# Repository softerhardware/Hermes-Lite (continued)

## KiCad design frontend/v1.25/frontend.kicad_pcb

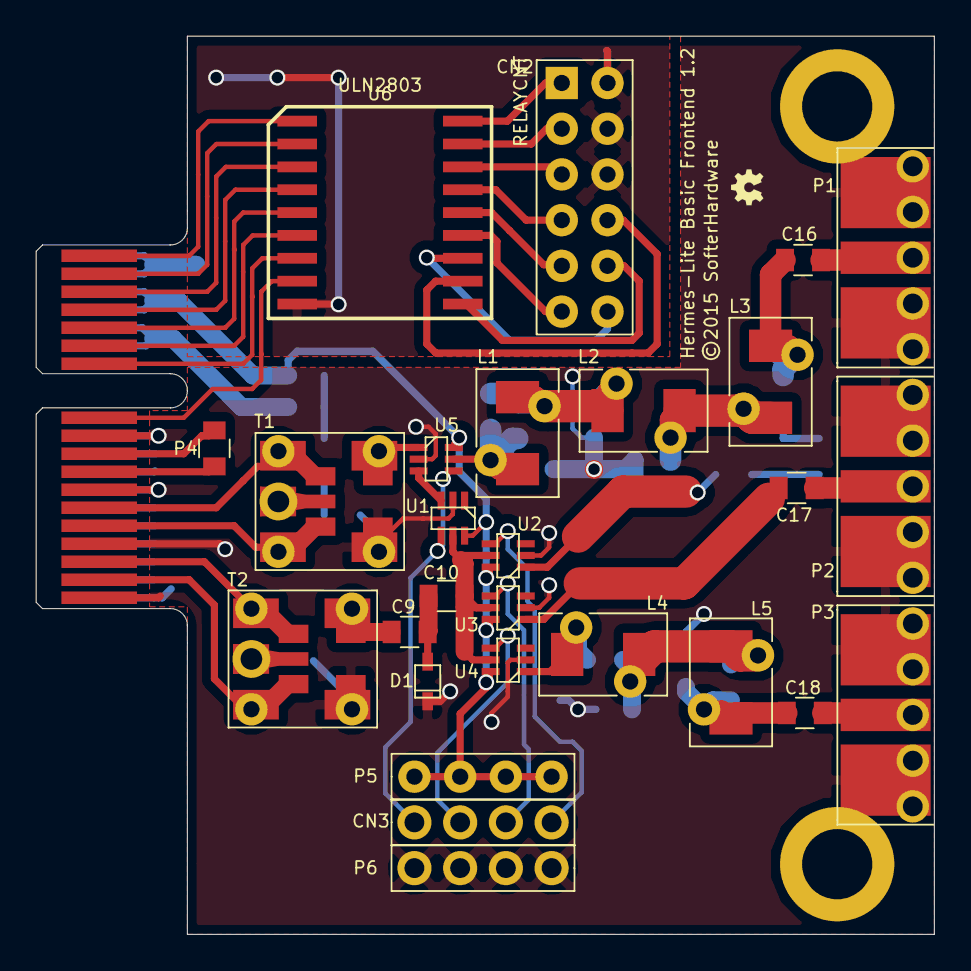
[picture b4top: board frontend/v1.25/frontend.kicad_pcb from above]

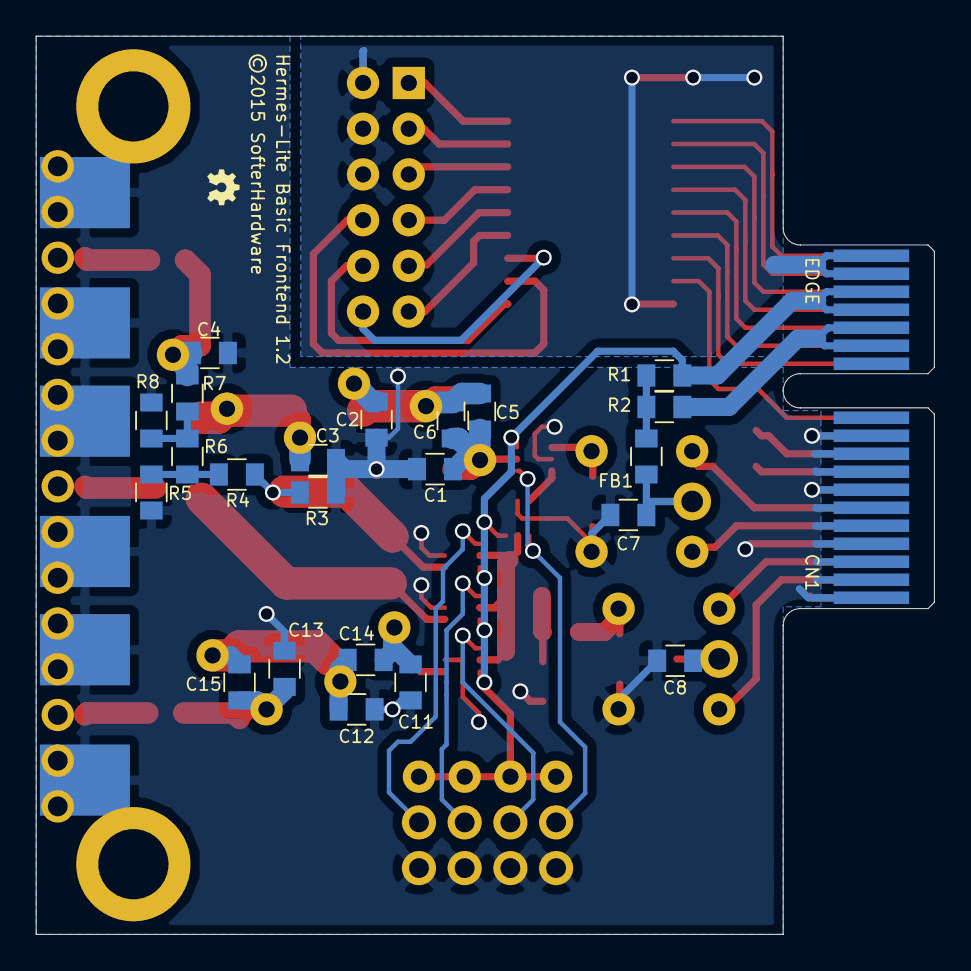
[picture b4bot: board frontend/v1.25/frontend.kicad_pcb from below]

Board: 2 copper layers, 49.9 x 49.9 mm, 52 parts (23 on the bottom side), 53 nets.

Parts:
C1: 110pF; C_0805
C2: 220pF; C_0805
C3: 160pF; C_0805
C4, C14, C15: DNI; C_0805
C5: 8.4pF; C_0805
C6: 75pF; C_0805
C7, C8, C9, C10, C16, C17, C18: 0.1uF; C_0805
C11, C13: 100pF; C_0805
C12: 180pF; C_0805
CN1: EDGE
CN2: RELAYCNT; BREAKOUT
CN3: RXCNT; 4pinmid
D1: DIODESCH2; SOD323
FB1: FB; C_0805
L1: 150nH; inductor
L2: 270nH; inductor
L3: 0H; inductor
L4, L5: 390nH; inductor
MH: VAL**; MH
MH#2: VAL**; MH
P1, P2, P3: SMA/BNC/HDR; rfconnector
P4: CONN_01X02; C_0805
P5, P6: CONN_01X04; 4pinmid
R1, R4: 0; C_0805
R2, R3: DNI; C_0805
R5: 87; C_0805
R6: 43; C_0805
R7: 2.2K; C_0805
R8: 76; C_0805
T1: 1:1; TRANSFSMT
T2: 8:1 Z; TRANSFSMT
U1, U2, U3, U4, U5: PE4259; pe4259
U6: ULN2803; PSOP-18

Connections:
3V: CN1.A15, CN1.A16, P5.1, P5.2, P5.3, P5.4, R1.1, U1.6, U2.6, U3.6, U4.6, U5.6
5V: CN1.A13, CN1.A14, R2.1
GND: C1.2, C2.2, C3.2, C4.2, C7.2, C8.2, C11.2, C12.2, C13.2, CN1.A1, CN1.A2, CN1.A3, CN1.A4, CN1.A5, CN1.A6, CN1.A7, CN1.A8, CN1.A9, CN1.A10, CN1.B1, CN1.B4, CN1.B7, CN1.B10, D1.2, P1.2, P2.2, P3.2, P6.1, P6.2, P6.3, P6.4, R3.2, R5.2, R8.2, T1.4, T2.4, U1.2, U2.2, U3.2, U4.2, U5.2
GNDREF: CN1.A17, CN1.A18, CN2.2, CN2.4, CN2.6, U6.9
unnamed: C1.1, C5.2, C6.2, L1.1, U5.5
unnamed: C2.1, C5.1, C6.1, L1.2, L2.1
unnamed: C3.1, L2.2, L3.1
unnamed: C7.1, FB1.1, T1.2
unnamed: C8.1, T2.2
unnamed: C9.2, T2.5
unnamed: C10.1, U1.5, U2.5, U3.5, U4.5
unnamed: C9.1, C10.2, D1.1
unnamed: C11.1, C14.2, L4.1, U4.1
unnamed: C12.1, C14.1, C15.2, L4.2, L5.1
unnamed: C13.1, C15.1, C18.1, L5.2
unnamed: C4.1, C16.1, L3.2, R7.2
unnamed: C16.2, P1.1
unnamed: C17.1, U3.1
unnamed: C17.2, P2.1
unnamed: C18.2, P3.1
unnamed: CN1.B2, T2.3
unnamed: CN1.B3, T2.1
unnamed: CN1.B5, T1.3
unnamed: CN1.B6, T1.1
unnamed: CN1.B8, P4.2
unnamed: CN1.B9, P4.1
unnamed: CN1.B11, U6.8
unnamed: CN1.B12, U6.7
unnamed: CN1.B13, U6.6
unnamed: CN1.B14, U6.5
unnamed: CN1.B15, U6.4
unnamed: CN1.B16, U6.3
unnamed: CN1.B17, U6.2
unnamed: CN1.B18, U6.1
unnamed: CN2.1, U6.18
unnamed: CN2.3, U6.17
unnamed: CN2.5, U6.16
unnamed: CN2.7, U6.15
unnamed: CN2.8, U6.11
unnamed: CN2.9, U6.14
unnamed: CN2.10, U6.10
unnamed: CN2.11, U6.13
unnamed: CN2.12, U6.12
unnamed: FB1.2, R1.2, R2.2
unnamed: R3.1, R4.2, U2.1
unnamed: R4.1, R5.1, R6.2
unnamed: R6.1, R7.1, R8.1
unnamed: T1.5, U5.1
unnamed: U1.3, U5.3
RX2: CN3.3, U3.4
RX3: CN3.2, U4.4
TAP: CN3.4, U2.4
TR: CN3.1, U1.4, U5.4

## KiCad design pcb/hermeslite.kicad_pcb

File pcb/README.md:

Hermes-Lite PCB
===============

This directory contains the following files document and build the Hermes-Lite hardware:

 * Kicad schematic
 * Kicad pcb 
 * High resolution photos of assembled prototoype (*.jpg)
 * BOM 
 * Gerber files for prototype
 * Gerber files for stencil

The Kicad project is named ad9866.pro. You may have to update paths fp-lib-table, ad9866.net, ad9866.pro and ad9866.xml to point to your install location. (Search for shaynal in these files and update.)

This hardware design is licensed under the TAPR open hardware license. See LICENSE.TXT for details.

## Additional Documentation ##

Analog Devices made a AD9866 evaluation board which is a helpful reference. The schematic is [here](http://www.analog.com/static/imported-files/eval_boards/AD9865_66_Schematics.pdf) and the layout is [here](http://www.analog.com/static/imported-files/eval_boards/AD9865_66_Layout.pdf).

Schematics and documentation for the BeMicro SDR can be found [here](http://www.alteraforum.com/forum/archive/index.php/t-30731.html)

A good paper on mixed signal PCB layout and analog grounds can be found [here](http://www.analog.com/library/analogdialogue/archives/46-06/staying_well_grounded.html)

## Assembly Experiences ##

I tried three assembly methods. At first, I thought I'd use an inexpensive stencil from OshStencils, solder paste and my infrawave toaster oven. I could never get the proper (minimum) amount of paste on the pcb because the large thermal via opening in the stencil under the AD9866 caused too much paste to be pushed under the stencil on to some pins. I scrapped this plan and went with hot air. (I have a $80 smt rework station that includes hot air. You can find them on e-bay or amazon.) I was eventually able to get hot air to work by following techniques you can find on youtube videos. The AD9866 moved around quite a bit. This prototype has problems that at different gain settings for the ADC I see excessive noise. I think I fried it during assembly. The last technique and the one I would recommend would be to slightly tin the AD9866 pads and thermal pad on the PCB with a regular iron and regular solder. Care must be taken to not use too much solder. Then, place the AD9866 and use a toaster oven to solder it in place. I then placed and soldered all the other components by hand. I choose a minimum size of 0805 to make this easy. It may be possible to place and solder the other SMT components along with the AD9866 in the toaster oven too. 

I think the last technique is within reach of most hams. You can buy an old toaster oven at a thrift shop for under $5. You can buy an oven thermometer at Wal-Mart for around $5. 

The AD9866 also requires baking at a low temperature for 24 hours to remove moisture. I also did this in the toaster oven but used too high a temperature on my first prototype. (Maybe that is why it didn't work.) With the oven thermometer, this is no problem.

## PCB ##
 * http://oshpark.com
 * http://www.hackvana.com
 * http://seeedstudio.com
 * http://elecrow.com
 * http://smart-prototyping.com

## PCBA ##
 * Seeedstudio will do PCBA if you use their open parts library
 * smart-prototyping will do PCBA and source parts for you
 * Bittele
 * http://www.myropcb.com
 * Many companies on alibaba

## Stencils ##
 * http://ohararp.com
 * http://www.oshstencils.com

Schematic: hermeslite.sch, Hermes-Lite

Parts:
C1, C2, C3, C4, C9, C10, C11, C15, C16, C22, C23, C24, C28, C29, C31, C32, C33, C34, C35, C36: 0.1UF; SMD-0805
C5, C6, C7, C8, C12, C13, C14, C17, C18, C21, C26, C27, C30: 1UF; SMD-0805
C19, C20: 10UF; SMD-1206_Pol
C25: 10UF; SMD-1206
CN1: MEC6-140_CONNECTOR_BEMICRO; MEC6-140-02-X-D-RAX
CN2: PCIE; PCIESTRADDLE
CN3: GPIO; EDGE6
CN4: POWER; EDGE6
FB1, FB2, FB3, FB4, FB5, FB6, FB7, FB8: FB; SMD-0805
J1, J2, J3, J4, J6: 0; SMD-0805
J5, J7, J8: 0; JUMPER
P0, P3, P5, P12: CONN_1; Measurement_Point_Round-TH_Small
P1: CONN_1
Palt0: CONN_1; Measurement_Point_Round-TH_Small
R1: 1.6K; SMD-0805
R2, R3: 200; SMD-0805
R4, R5: 47; SMD-0805
S1, S2, S3: CONN_1; Measurement_Point_Round-TH_Small
TP1, TP2, TP3, TP4, TP5, TP6: CONN_1; TP
U1: AD9866BCPZ; CP_64_3-M
U2: EEPROM; SOT-23-6
X1: 73.728; Si510

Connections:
3VIN: C15.1, C16.1, C17.1, C18.1, C19.1, C20.1, CN4.6, CN4.8, FB1.1, FB2.1, FB3.1, FB4.1, J7.2, P3.1
5VIN: C21.1, C22.1, C27.1, C35.1, CN4.2, CN4.4, FB5.1, FB7.1, P5.1
12VIN: C30.1, C36.1, CN4.10, CN4.12, FB8.1, P12.1
/PTT#: CN1.50 (P53), CN1.73 (NC), CN2.B11
/RXN: C31.1, CN2.B2
/RXP: C32.1, CN2.B3
/TXLN: CN2.B8, R3.2, U1.51 (IOUT_P-)
/TXLP: CN2.B9, R3.1, U1.52 (IOUT_P+)
/TXN: CN2.B5, J2.1, R2.2, U1.46 (IOUT_N-)
/TXP: CN2.B6, J1.1, R2.1, U1.50 (IOUT_N+)
/USEROUT0: CN1.52 (P54), CN1.75 (NC), CN2.B12
/USEROUT1: CN1.56 (P55), CN2.B13
/USEROUT2: CN1.58 (P56), CN2.B14
/USEROUT3: CN1.60 (P57), CN2.B15
/USEROUT4: CN1.62 (P58), CN2.B16
/USEROUT5: CN1.64 (P59), CN2.B17
/USEROUT6: CN1.66 (P60), CN2.B18
AVDD_ADC: C1.1, C5.1, C9.1, C12.1, FB1.2, U1.35 (AVDD_2), U1.40 (AVDD_1)
AVDD_DAC: C10.1, C13.1, FB2.2, U1.43 (AVDD)
CLKVDD: C2.1, C6.1, FB3.2, U1.58 (CLKVDD), X1.4
DVDD: C3.1, C4.1, C7.1, C8.1, C11.1, C14.1, C26.1, C33.2, C34.1, CN1.78 (EXP_PRESENT), FB4.2, FB6.1, U1.17 (DRVDD), U1.60 (DVDD), U1.64 (DRVDD_1), U2.6
EXP3V: CN2.A15, CN2.A16, FB6.2
EXP5V: CN2.A13, CN2.A14, FB7.2
EXP12V: CN2.A11, CN2.A12, FB8.2
FPGA5V: CN1.79 (5V), CN1.80 (5V), J8.1
GND: C1.2, C2.2, C3.2, C4.2, C5.2, C6.2, C7.2, C8.2, C9.2, C10.2, C11.2, C12.2, C13.2, C14.2, C15.2, C16.2, C17.2, C18.2, C19.2, C20.2, C21.2, C22.2, C23.2, C26.2, C27.2, C28.2, C29.2, C30.2, C33.1, C34.2, C35.2, C36.2, CN1.10 (GND), CN1.21 (GND), CN1.22 (GND), CN1.32 (AGND), CN1.33 (GND), CN1.44 (GND), CN1.53 (GND), CN1.54 (GND), CN1.76 (GND), CN2.A1, CN2.A2, CN2.A3, CN2.A4, CN2.A5, CN2.A6, CN2.A7, CN2.A8, CN2.A9, CN2.A10, CN2.A17, CN2.A18, CN2.B1, CN2.B4, CN2.B7, CN2.B10, CN3.1, CN4.1, CN4.3, CN4.5, CN4.7, CN4.9, CN4.11, J5.1, P0.1, P1.1, Palt0.1, R1.1, R4.2, R5.1, U1.18 (DRVSS_1), U1.31 (AVSS_3), U1.34 (AVSS_2), U1.36 (AVSS_1), U1.39 (AVSS), U1.44 (AVSS_6), U1.47 (AVSS_5), U1.48 (AVSS_4), U1.54 (CONFIG), U1.55 (CLKVSS), U1.59 (DVSS), U1.62 (PWR_DWN), U1.63 (DRVSS), U1.65 (EP), U2.2, X1.1, X1.2
MCSn: CN1.36 (P47), U2.5
MSCK: CN1.24 (P42), U2.1
MSI: CN1.26 (P43), U2.3
MSO: CN1.34 (P46), U2.4
unnamed: C23.1, U1.42 (REFIO)
unnamed: C24.1, C25.1, C28.1, U1.33 (REFT)
unnamed: C24.2, C25.2, C29.1, U1.32 (REFB)
unnamed: C31.2, U1.37 (RX-)
unnamed: C32.2, U1.38 (RX+)
unnamed: CN1.1 (3V3), CN1.2 (3V3), J7.1
unnamed: CN1.3 (RESET_EXP#), U1.30 (RESET*)
unnamed: CN1.4 (PWREN#), J5.2
unnamed: CN1.5 (P1), J3.2
unnamed: CN1.6 (P35), J6.1, R4.1, U1.16 (RXCLK)
unnamed: CN1.7 (P2), TP1.1
unnamed: CN1.8 (P36), TP6.1
unnamed: CN1.9 (P3), CN3.10
unnamed: CN1.11 (P4), U1.29 (PGA[0])
unnamed: CN1.12 (P37), CN3.2
unnamed: CN1.13 (P5), U1.28 (PGA[1])
unnamed: CN1.14 (P38), CN3.4
unnamed: CN1.15 (P6), U1.27 (PGA[2])
unnamed: CN1.16 (P39), CN3.3
unnamed: CN1.17 (P7), U1.26 (PGA[3])
unnamed: CN1.18 (P40), CN3.6
unnamed: CN1.19 (P8), U1.25 (PGA[4])
unnamed: CN1.20 (P41), CN3.5
unnamed: CN1.23 (P9), U1.24 (GAIN/PGA[5])
unnamed: CN1.25 (P10), U1.23 (SEN*)
unnamed: CN1.27 (P11), U1.22 (SCLK)
unnamed: CN1.28 (P44), CN3.8
unnamed: CN1.29 (P12), U1.21 (SDO)
unnamed: CN1.30 (P45), CN3.7
unnamed: CN1.31 (P13), U1.20 (SDIO)
unnamed: CN1.35 (P14), U1.15 (TXCLK/TXQUIET*)
unnamed: CN1.37 (P15), U1.14 (TXEN/TXSYNC)
unnamed: CN1.38 (P48), TP5.1
unnamed: CN1.39 (P16), U1.13 (RXEN/RXSYNC)
unnamed: CN1.40 (P49), J6.2
unnamed: CN1.41 (P17), U1.12 (ADIO0/Rx[0])
unnamed: CN1.42 (P50), TP4.1
unnamed: CN1.43 (P18), U1.11 (ADIO1/Rx[1])
unnamed: CN1.45 (P19), U1.10 (ADIO2/Rx[2])
unnamed: CN1.46 (P51), J4.1
unnamed: CN1.47 (P20), U1.9 (ADIO3/Rx[3])
unnamed: CN1.48 (P52), TP3.1
unnamed: CN1.49 (P21), U1.8 (ADIO4/Rx[4])
unnamed: CN1.51 (P22), U1.7 (ADIO5/Rx[5])
unnamed: CN1.55 (P23), U1.6 (ADIO6/Tx[0])
unnamed: CN1.57 (P24), U1.5 (ADIO7/Tx[1])
unnamed: CN1.59 (P25), U1.4 (ADIO8/Tx[2])
unnamed: CN1.61 (P26), U1.3 (ADIO9/Tx[3])
unnamed: CN1.63 (P27), U1.2 (ADIO10/Tx[4])
unnamed: CN1.65 (P28), U1.1 (ADIO11/Tx[5])
unnamed: CN1.67 (P29), TP2.1, U1.53 (MODE)
unnamed: CN3.9, S1.1
unnamed: CN3.11, S2.1
unnamed: CN3.12, S3.1
unnamed: FB5.2, J8.2
unnamed: J1.2, U1.49 (IOUT_G+)
unnamed: J2.2, U1.45 (IOUT_G-)
unnamed: J3.1, J4.2, R5.2, U1.19 (CLKOUT1)
unnamed: R1.2, U1.41 (REFADJ)
unnamed: U1.57 (OSCIN), X1.3

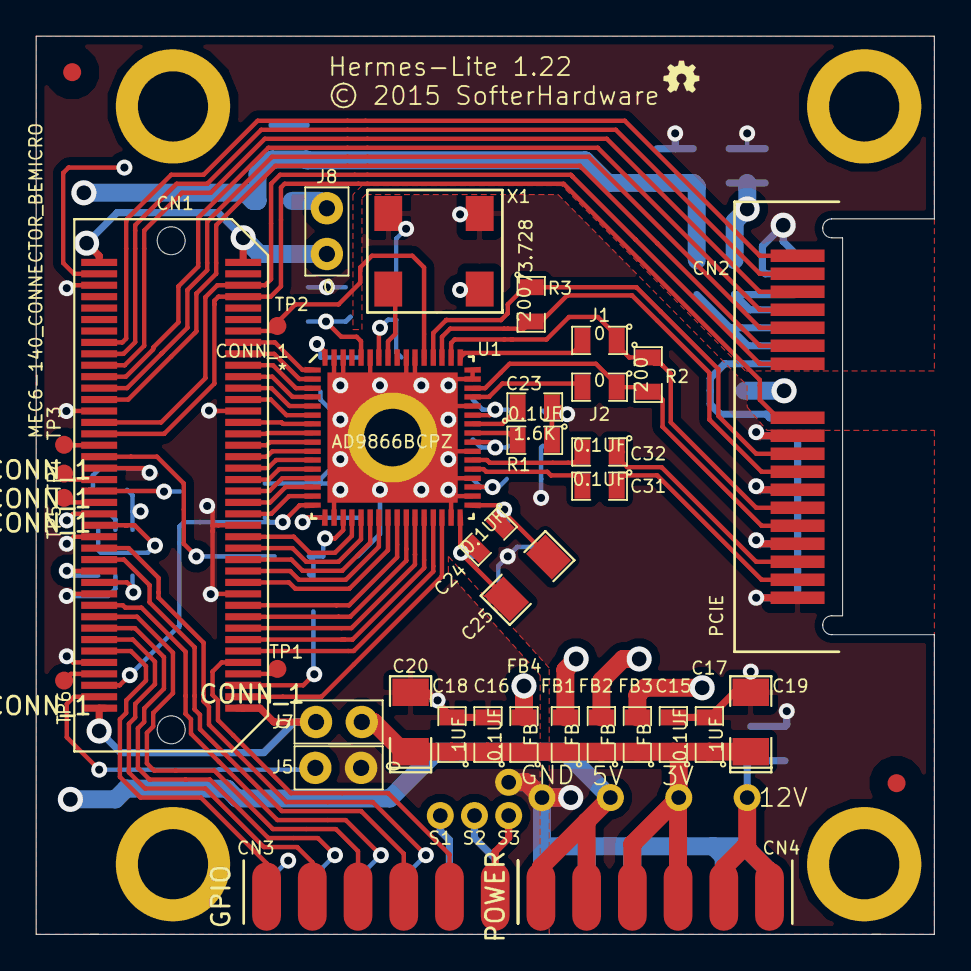
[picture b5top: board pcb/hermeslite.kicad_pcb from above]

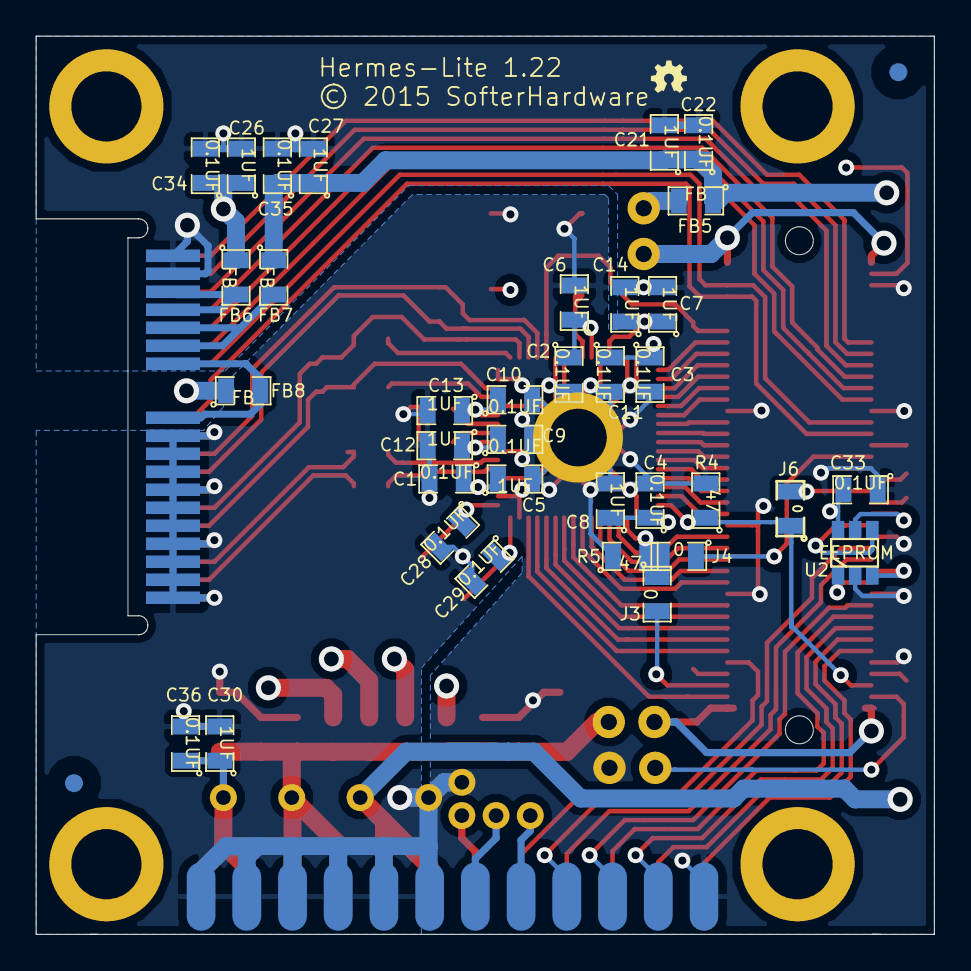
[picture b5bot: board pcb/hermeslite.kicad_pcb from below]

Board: 4 copper layers, 49.9 x 49.9 mm, 87 parts (37 on the bottom side), 90 nets.

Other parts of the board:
FIDUCIAL: VAL**; FIDUCIAL
FIDUCIAL#2, FIDUCIAL#3, FIDUCIAL#4: VAL**; FIDUCIAL
MH: VAL**; MH
MH#2, MH#3, MH#4: VAL**; MH

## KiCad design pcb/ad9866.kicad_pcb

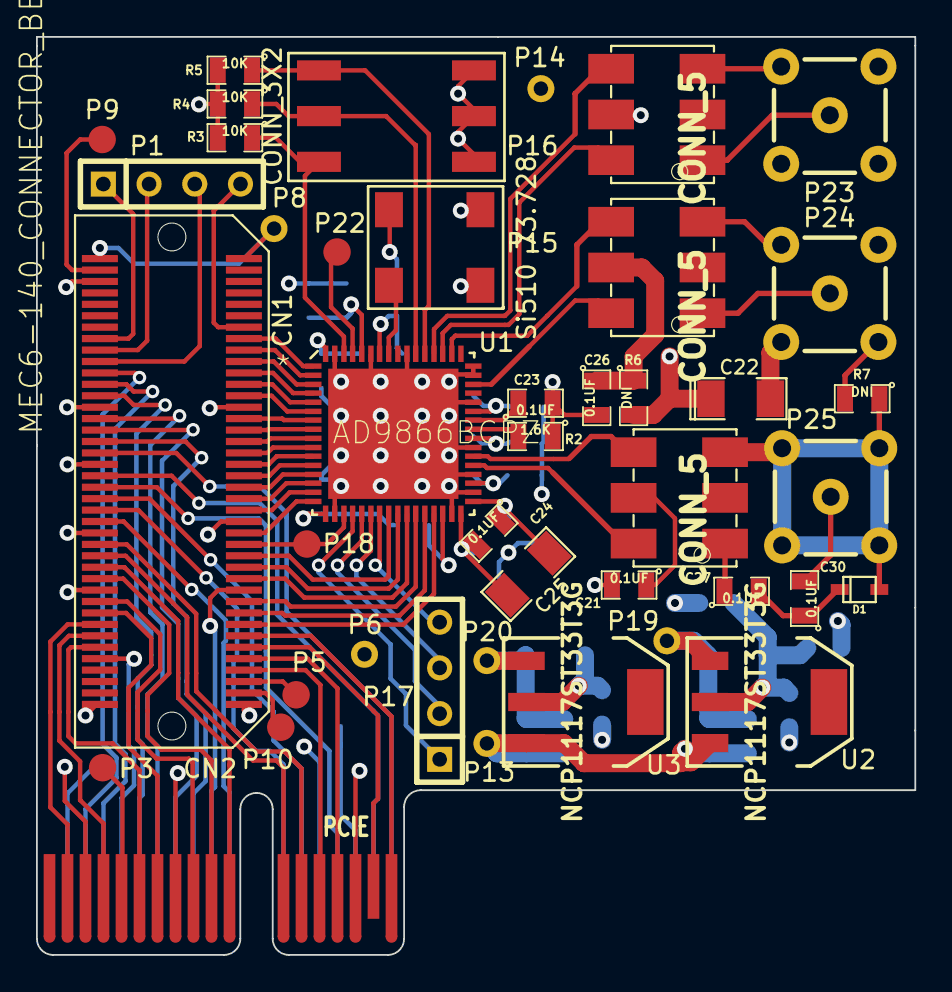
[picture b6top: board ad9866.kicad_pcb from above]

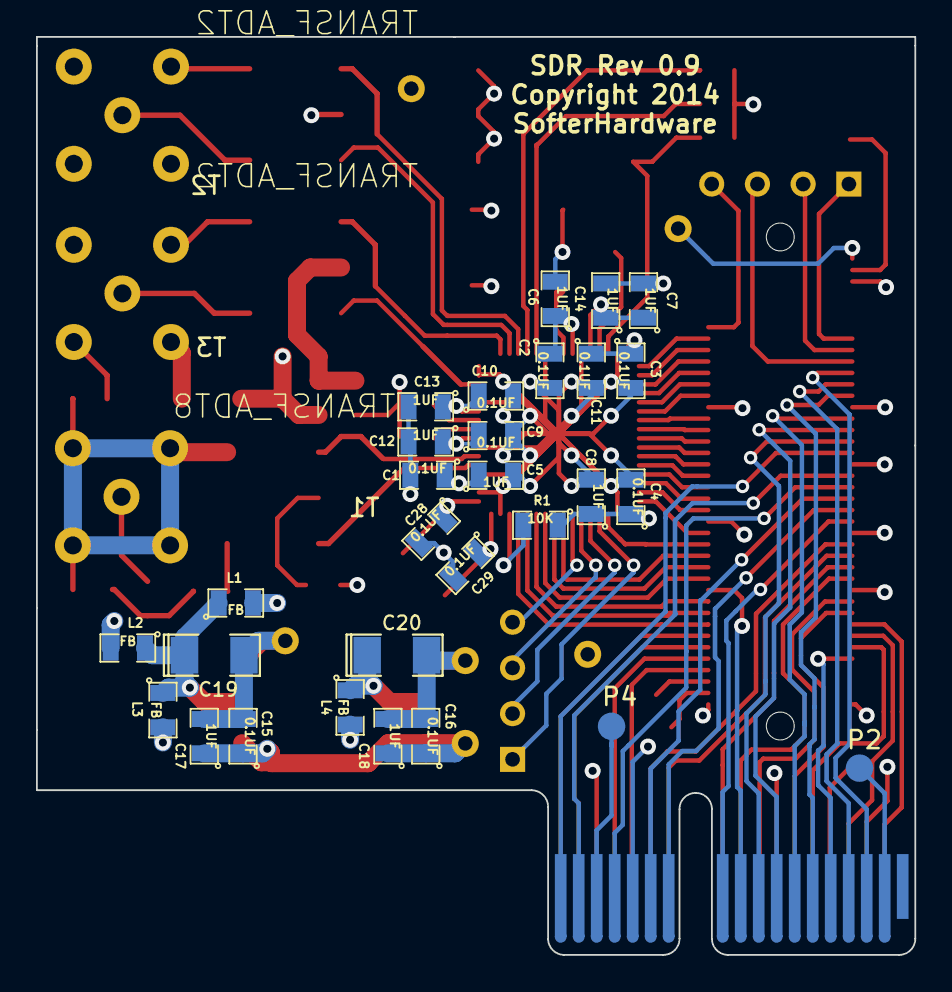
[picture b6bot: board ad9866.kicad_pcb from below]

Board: 4 copper layers, 48.8 x 51.0 mm, 71 parts (29 on the bottom side), 96 nets.

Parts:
C1, C2, C3, C4, C9, C10, C11, C15, C16, C21, C23, C24, C26, C27, C28, C29, C30: 0.1UF; SM0805
C5, C6, C7, C8, C12, C13, C14, C17, C18: 1UF; SM0805
C19, C20, C22: 10UF; SM1206POL
C25: 10UF; SM1206
CN1: MEC6-140_CONNECTOR_BEMICRO; MEC6-140-02-X-D-RAX
CN2: PCIE; PCI-EXPRESS
D1: CDSOD323; SOD323
L1, L2, L3, L4: FB; SM0805
P1, P17: CONN_4; SIL-4
P2, P3, P4, P5, P9, P10, P18, P22: CONN_1; Measurement_Point_Round-SMD-Pad_Small
P6, P8, P13, P14, P19, P20: CONN_1; Measurement_Point_Round-TH_Small
P15: Si510 73.728; Si510
P16: CONN_3X2; DIPSWITCH
P23, P24, P25: CONN_5; SMA
R1, R3, R4, R5: 10K; SM0805
R2: 1.6K; SM0805
R6, R7: DNI; SM0805
T1: TRANSF_ADT8; minicircuits-CD542
T2, T3: TRANSF_ADT2; minicircuits-CD542
U1: AD9866BCPZ; CP_64_3-M
U2, U3: NCP1117ST33T3G; SOT223

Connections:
AVDD_ADC: C1.1, C5.1, C9.1, C12.1, L1.2, U1.35, U1.40
AVDD_DAC: C10.1, C13.1, L2.2, U1.43
CLKVDD: C2.1, C6.1, L3.2, P15.4, U1.58
DVDD: C3.1, C4.1, C7.1, C8.1, C11.1, C14.1, L4.2, P16.1, P16.3, P16.5, R1.1, U1.17, U1.60, U1.64
GND: C1.2, C2.2, C3.2, C4.2, C5.2, C6.2, C7.2, C8.2, C9.2, C10.2, C11.2, C12.2, C13.2, C14.2, C15.2, C16.2, C17.2, C18.2, C19.2, C20.2, C21.2, C22.2, C23.2, C26.2, C28.2, C29.2, CN1.10, CN1.21, CN1.22, CN1.32, CN1.33, CN1.44, CN1.53, CN1.54, CN1.76, CN2.A5, CN2.A10, CN2.A14, CN2.B3, CN2.B8, CN2.B16, P15.1, P15.2, P19.1, P20.1, P23.2, P23.3, P23.4, P23.5, P24.2, P24.3, P24.4, P24.5, R2.1, R3.2, R4.2, R5.2, R7.2, T2.3, T2.5, T3.3, U1.18, U1.31, U1.34, U1.36, U1.39, U1.44, U1.47, U1.48, U1.55, U1.59, U1.63, U1.65, U2.1, U3.1
unnamed: C19.1, L1.1, L2.1, L3.1, U2.2
unnamed: C20.1, L4.1, U3.2
unnamed: C21.1, T1.5
unnamed: C23.1, U1.42
unnamed: C24.1, C25.1, C28.1, U1.33
unnamed: C24.2, C25.2, C29.1, U1.32
unnamed: C26.1, R6.1, T3.5
unnamed: C27.1, T1.1
unnamed: C27.2, C30.1, D1.2
unnamed: C30.2, P25.1
unnamed: CN1.1, CN1.2, P6.1
unnamed: CN1.3, P10.1
unnamed: CN1.5, P5.1
unnamed: CN1.7, CN2.B14
unnamed: CN1.9, CN2.B15
unnamed: CN1.11, CN2.B17
unnamed: CN1.12, CN2.B6
unnamed: CN1.13, CN2.B18
unnamed: CN1.14, CN2.B4
unnamed: CN1.15, U1.29
unnamed: CN1.16, CN2.B2
unnamed: CN1.17, U1.28
unnamed: CN1.18, CN2.B7
unnamed: CN1.19, U1.27
unnamed: CN1.20, CN2.B9
unnamed: CN1.23, U1.26
unnamed: CN1.24, CN2.B10
unnamed: CN1.25, U1.25
unnamed: CN1.26, CN2.B11
unnamed: CN1.27, U1.24
unnamed: CN1.28, CN2.B12
unnamed: CN1.29, P18.1, U1.19
unnamed: CN1.30, CN2.B13
unnamed: CN1.31, U1.16
unnamed: CN1.34, CN2.A11
unnamed: CN1.35, U1.15
unnamed: CN1.36, CN2.A12
unnamed: CN1.37, U1.14
unnamed: CN1.38, CN2.A13
unnamed: CN1.39, U1.13
unnamed: CN1.40, CN2.A15
unnamed: CN1.41, U1.12
unnamed: CN1.42, CN2.A17
unnamed: CN1.43, U1.11
unnamed: CN1.45, U1.10
unnamed: CN1.46, CN2.A18
unnamed: CN1.47, U1.9
unnamed: CN1.48, CN2.A9
unnamed: CN1.49, U1.8
unnamed: CN1.50, CN2.A8
unnamed: CN1.51, U1.7
unnamed: CN1.52, CN2.A7
unnamed: CN1.55, U1.6
unnamed: CN1.56, CN2.A6
unnamed: CN1.57, U1.5
unnamed: CN1.58, CN2.A4
unnamed: CN1.59, U1.4
unnamed: CN1.60, CN2.A3
unnamed: CN1.61, U1.3
unnamed: CN1.62, P1.3
unnamed: CN1.63, U1.2
unnamed: CN1.64, P1.2
unnamed: CN1.65, U1.1
unnamed: CN1.66, P1.1
unnamed: CN1.67, P1.4
unnamed: CN1.78, P9.1
unnamed: CN1.79, CN1.80, P8.1
unnamed: CN2.A2, P2.1
unnamed: CN2.A16, P4.1
unnamed: CN2.B5, P3.1
unnamed: D1.1, P25.2, P25.3, P25.4, P25.5, R7.1, T1.3
unnamed: P15.3, U1.57
unnamed: P16.2, R3.1, U1.62
unnamed: P16.4, R4.1, U1.54
unnamed: P16.6, R5.1, U1.53
unnamed: P22.1, U1.61
unnamed: P23.1, T2.1
unnamed: P24.1, T3.1
unnamed: R1.2, U1.30
unnamed: R2.2, U1.41
unnamed: T2.4, U1.52
unnamed: T2.6, U1.51
unnamed: T3.4, U1.50
unnamed: T3.6, U1.46
RXN: T1.6, U1.37
RXP: T1.4, U1.38
SCLK: P17.3, U1.22
SDIO: P17.1, U1.20
SDO: P17.2, U1.21
SEN: P17.4, U1.23
VIN: C15.1, C16.1, C17.1, C18.1, C22.1, P13.1, P14.1, R6.2, U2.3, U3.3

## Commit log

2014-04-13 Fixed a few typos, added demo
2014-04-13 Clarified README
2014-04-16 Update README.md
    Edit demo information
2014-04-20 Update README.md
    Added development information.
2014-04-20 Added more assembly info
2014-04-20 Fixed Header
2014-04-20 Added "Staying Well Grounded"
2014-05-26 Added support for 2 receivers
2014-08-25 Schematic rev 1.1a
2014-08-28 Added modified and pci36
2014-09-01 Before library and name changes
2014-09-02 Rev 1.1b schematic, footprint library, and library cleanup
2014-09-08 RTL cleanup and upgrade to Quartus 14.0
2014-09-08 More RTL cleanup
2014-09-10 Added RTL revisions for 09SDK and 09CV
2014-09-12 Added test files
2014-09-12 Updates to stock firmware to address clock issues
2014-09-14 Added Verilog for Tests
2014-10-01 Intermediate save before move of PCIe connector
2014-10-05 Commit before silkscreen cleanup
2014-10-05 Version 1.2 for review
2014-10-08 Updated BOM, renumbered a few references
2014-10-09 iTead Studio submission
2014-10-19 Added SDK testclocks for NoAD9866 compilation
2014-10-20 Added RF frontend template and basic
2014-10-24 Added WaveShare2BeMicroCV swizzle board
2014-11-11 Test Files for BeMicro CV with WaveShare
2014-11-19 Added PDF
2014-11-20 New Picture
2014-11-20 typo
2014-11-22 Added links to interesting forks
2014-11-27 Updated basic frontend
2014-12-01 Added CV support
2014-12-01 Added missing files
2014-12-09 Added revision 1.21
2014-12-09 updated schematic
2014-12-18 Updated pcb BOM and kit BOM
2014-12-21 Documentation pointer update
2014-12-21 Updated main page
2014-12-29 Added AGC, versioned bit files
2015-01-05 Transfer from laptop, work on CV
2015-01-09 Fix for bom
2015-01-11 Updated README.md with new picture
2015-01-11 Added new picture
2015-01-11 Remove pipeline in agc, experiments with compile time
2015-01-12 Updated frontend schematic to match build instructions
2015-01-16 Support for 384kHz and fix for TX sideband spurs
2015-01-17 WIP on filtering
2015-01-19 v20150118: exp_ptt_n support, +12db to match Hermes, plumbing for ad9866clkX2
2015-01-19 Added Tindie
2015-01-21 Added userout[6:0]
2015-01-21 Updated schematics for user[6:0]
2015-01-22 Added UNL2003 and connectors
2015-01-25 Revert "Added UNL2003 and connectors"
2015-01-26 Release 20150125, test mode works again, ADC overload to software, tweaks to AGC
2015-02-04 Recalculate for 12-bit RX path, overload hooked up tolonger LEDs, PTT matches Hermes
2015-02-06 Gain to match PowerSDR, AGC gain tracks manual gain setting, increased timeout on AGC, proper inversion of ADC overload
2015-02-06 Updated frontend xls with kit binocular core part
2015-02-07 Added version for BeMicro CV C8
2015-02-08 Patch all relevant code to v3.1 of Hermes
2015-02-11 Added patches to Hermes v3.1, target CV C8 device, constrained some external FPGA to ADC pins
2015-02-11 Added 20150210
2015-02-16 Add TX Drive level, Hermes-Lite board ID, increased user IO drive, tweaked frequency calibration
2015-02-18 20150217: Some timing fixes, increased current on ptt
2015-02-23 20150222: Full TX gain range, better timing closure on FPGA/ethernet paths
2015-03-02 Work on timing bug
2015-03-05 Timing constraint for 20150304 release
2015-03-05 Release 20150304: more stable
2015-03-16 Removed ASMI
2015-03-16 Added first 3D printer files
2015-03-19 Rx_MAC refactoring
2015-03-22 Refactoring of MACs
2015-03-26 Updated BOM with new oscillator part number
2015-03-30 3RX on SDK, constant current TX gain adjustment, no ASMII
2015-03-31 Bitfiles for release 20150330
2015-04-13 Added support for ADC measurements via SPI
2015-05-14 Added support for 73.728 oscillator
2015-05-18 20150517: 73.728 support, multiple MAC, SPI ADC, refactoring
2015-05-19 Added Hermes_ADC.v
2015-05-23 Small change for v1.21 tag
2015-05-24 Added gerber for v1.22
2015-05-24 Updated Readme.md for v1.22
2015-06-10 Release 20150609
2015-06-12 Added support for CVA9
2015-06-14 Changed address for RX8 to not collide with existing protocol
2015-06-14 Updated CVA9 .jic file
2015-06-29 Full duplex and other work in progress
2015-07-05 Added multiple transmitters, see paramter NT in hermes_lite_cores.v
2015-07-05 Added Power Amplifiers
2015-07-07 Updated frequency information
2015-07-09 DHCP Fix
2015-07-15 Noise cleanup in FD
2015-07-26 cleanup and combine FD with HD
2015-07-27 Save IP support, CW support, cleanup
2015-07-28 Fix for test bug in full duplex
2015-07-30 Firmware 20150729
2015-08-09 Gigabit ethernet support for CVA9
2015-08-10 Updated README to include v2.0 architecture
2015-08-17 Changes before patching to 32 receivers from N1GP
2015-08-17 Gigabit cleanup, DHCP fixes
2015-08-21 Accept frequency change even if receiver is off
2015-08-27 TX fix for CVA9 gigabit
2015-08-27 Added CVA9 beta
2015-09-06 Patch from NO1D to fix skimmer problem, make IP more like old protocol
2015-09-06 Added new beta .jic for CVA9
2015-09-08 Added new test frontend
2015-09-14 Updated Schematic, floorplanning
2015-09-21 New frontend board
2015-09-21 Added gerber
2015-09-21 external pttin test
2015-09-21 Proper pin placement
2015-10-13 Merging changes
2015-10-13 Pure signal support, CVA9 fullduplex, icmp destination unreachable fix, external ptt, v2 frontend gerber, spectrum analyzer scripts
2015-10-18 Fix to keep host IP and MAC
2015-10-18 Firmware 20151018
2015-12-06 Updated links
2015-12-16 Added Alan's Experimental Predistortion, some timing tweaks
2015-12-20 Added nco and cordic work
2016-01-02 Use TxPGA directly
    Removed the initialization of register 0x10 to leave the default
    value, so the TxPGA code is not corrupted.
    Removed also the code updating that register when changing the TX drive
    level for the same reason.
    Removed the look-up table that translated the 0:255 TX drive code to
    the 0:39 TxPGA code and replaced with a simple formula giving no
2016-01-18 Program parameters for SPI, RX support for 79.872, work on better timing closure
2016-02-08 Added 76.8MHz support, expanded initarrays, some timing tweaks
2016-02-11 Added v1.3 frontend from Jim
2016-02-11 Added ad9866.v
2016-02-14 Support to disable IAMP, fix in ad9866 for TX level bug
2016-02-14 Fix for sampling external request only every other clock tick
2016-02-21 V2 prep
2016-02-21 Added TxDAC bitfiles
2016-02-22 More v2 prep
2016-02-22 Removed bitfiles
2016-03-05 Update before trip
2016-03-23 Work on power schematic
2016-04-04 Updated with InputOutput
2016-04-12 Added 5 IC footprints, local path for library
2016-04-19 Footprint work, 18 new footprints
2016-04-21 New Ethernet DHCP fixes and improvements from Jim N2ADR. Adheres more to RFC.
2016-04-21 Updated fp_lib_table with no local path
2016-04-21 Removed v1.22 bitfiles
2016-04-22 Added frontend V1.42 from Jim
2016-04-26 Footprints, initial floor and wire planning
2016-05-09 More floor and wire planning
2016-05-17 Fix for TX above 19dB in fullduplex, update libraries to Quartus 16.0
2016-05-23 Frontend work
2016-05-23 Support for two initarrays, timing as bits on rx signals
2016-05-30 RF Frontend refinements
2016-05-31 New floorplan
2016-06-06 Push of new work
2016-07-02 Work towards Cyclone IV
2016-07-08 Work on V2
2016-07-11 Added filters and PA
2016-07-11 Added PTT out, internal IO
2016-07-18 Work on powersupply
2016-07-18 Updated annotation and regenerated pdf
2016-07-28 Added test pa
2016-07-28 Added pdf and png files
2016-07-30 RF output fix on testpa
2016-07-30 Silk screen sizes, copyright notice
2016-07-31 Final PCBs, added gerber
2016-08-02 Added JI1UDD Link
2016-08-12 Added BOM
2016-08-16 Removed BOM
2016-08-22 Latest v2 work
2016-08-22 Added bom tools
2016-08-27 Before Power Supply Change
2016-08-29 More PCB layout
2016-09-08 Update, more layout
2016-09-09 More layout
2016-09-12 Additional layout work
2016-09-19 Updates to layout
2016-09-27 Layout and routing work
2016-10-08 Latest filter values
2016-10-17 Updated schematics
2016-10-29 Latest layout
2016-10-30 Before silk cleanup
2016-10-31 Layout silkscreen
2016-11-03 Ground plane work
2016-11-06 Before clock rework
2016-11-07 Commit for printing
2016-11-07 Before ethernet phy rework
2016-11-14 Hermes-Lite 2.0beta2
2016-11-14 Beta2 schematic
2016-11-18 BOM work
2016-11-18 Updated pricing info
2016-11-21 Added options
2016-11-21 Latex updates
2016-11-21 Option fixes
2016-11-21 More BOM work
2016-11-22 BOM release
2016-11-24 Switch to 2.x
2016-11-27 Link to web page
2016-12-01 Added a second VNA method; the FPGA scans the frequencies itself
2016-12-03 VNA: refactored to isolate changes to one module
2016-12-07 VNA polished, Hermes_serialno=32, released to bitfiles/20161207
2017-01-09 Changed the DHCP renewal process to more closely agree with the RFC.
2017-01-10 fix error on last data byte of wideband and receiver packets
